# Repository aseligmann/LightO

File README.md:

# LightO

LightO is an open remote-controlled light project.

The project is based around an ESP32 driving a string of addressable LEDs, in this case a custom PCB with 61 SK6812 RGBW LEDs.

The user is able to control the LightO through an intuitive web-based interface, consisting of color-wheel and slider control.
The brightness of the light is user-controlled and can be driven at up to roughly 15 W, for an eye-scorching brightness level.

The LightO has 3 modes which can be selected from the interface:

* **Colour** - User defines a colour to display
* **Candle** - Simulates a flickering candle
* **Cycle** - Cycles through the colour-spectrum

The light is powered by a single USB-C port. 

### Images

### Features
- Full control of colour and brightness (RGBW channels) for all LEDs
- USB-C powered
- WiFi based control with user-centered design
- Intuitive captive AP for setup

### Development
- [ ] Provide schematic for ESP32 piggyback board
- [ ] Wake-up mode simulating a sunrise at a userdefined time
- [ ] Migrate code to PlatformIO
- [ ] Integrate USB-C PD and ESP32 on LED PCB

### Bill of Materials

#### PCB
* 1x 160 mm LightO PCB (light_160mm_v1_0_2020-04-21)
* 61x SK6812 LEDs
* 61x 5050 LED lenses, wide angle (optional)
* 61x 0805 100 nF capacitors
* 2x JST-XH 2-pin straight connectors

#### ESP32
* 1x ESP32 development board
* 1x 100 uF capacitor
* 2x 330 Ohm resistors

#### Power-delivery
* 1x USB-C PD module (ZY12PDN)

#### Misc.
* 7x M3 bolts (16 mm)
* 7x M3 nuts
* 3x 2.2x9.5 self-tapping screws

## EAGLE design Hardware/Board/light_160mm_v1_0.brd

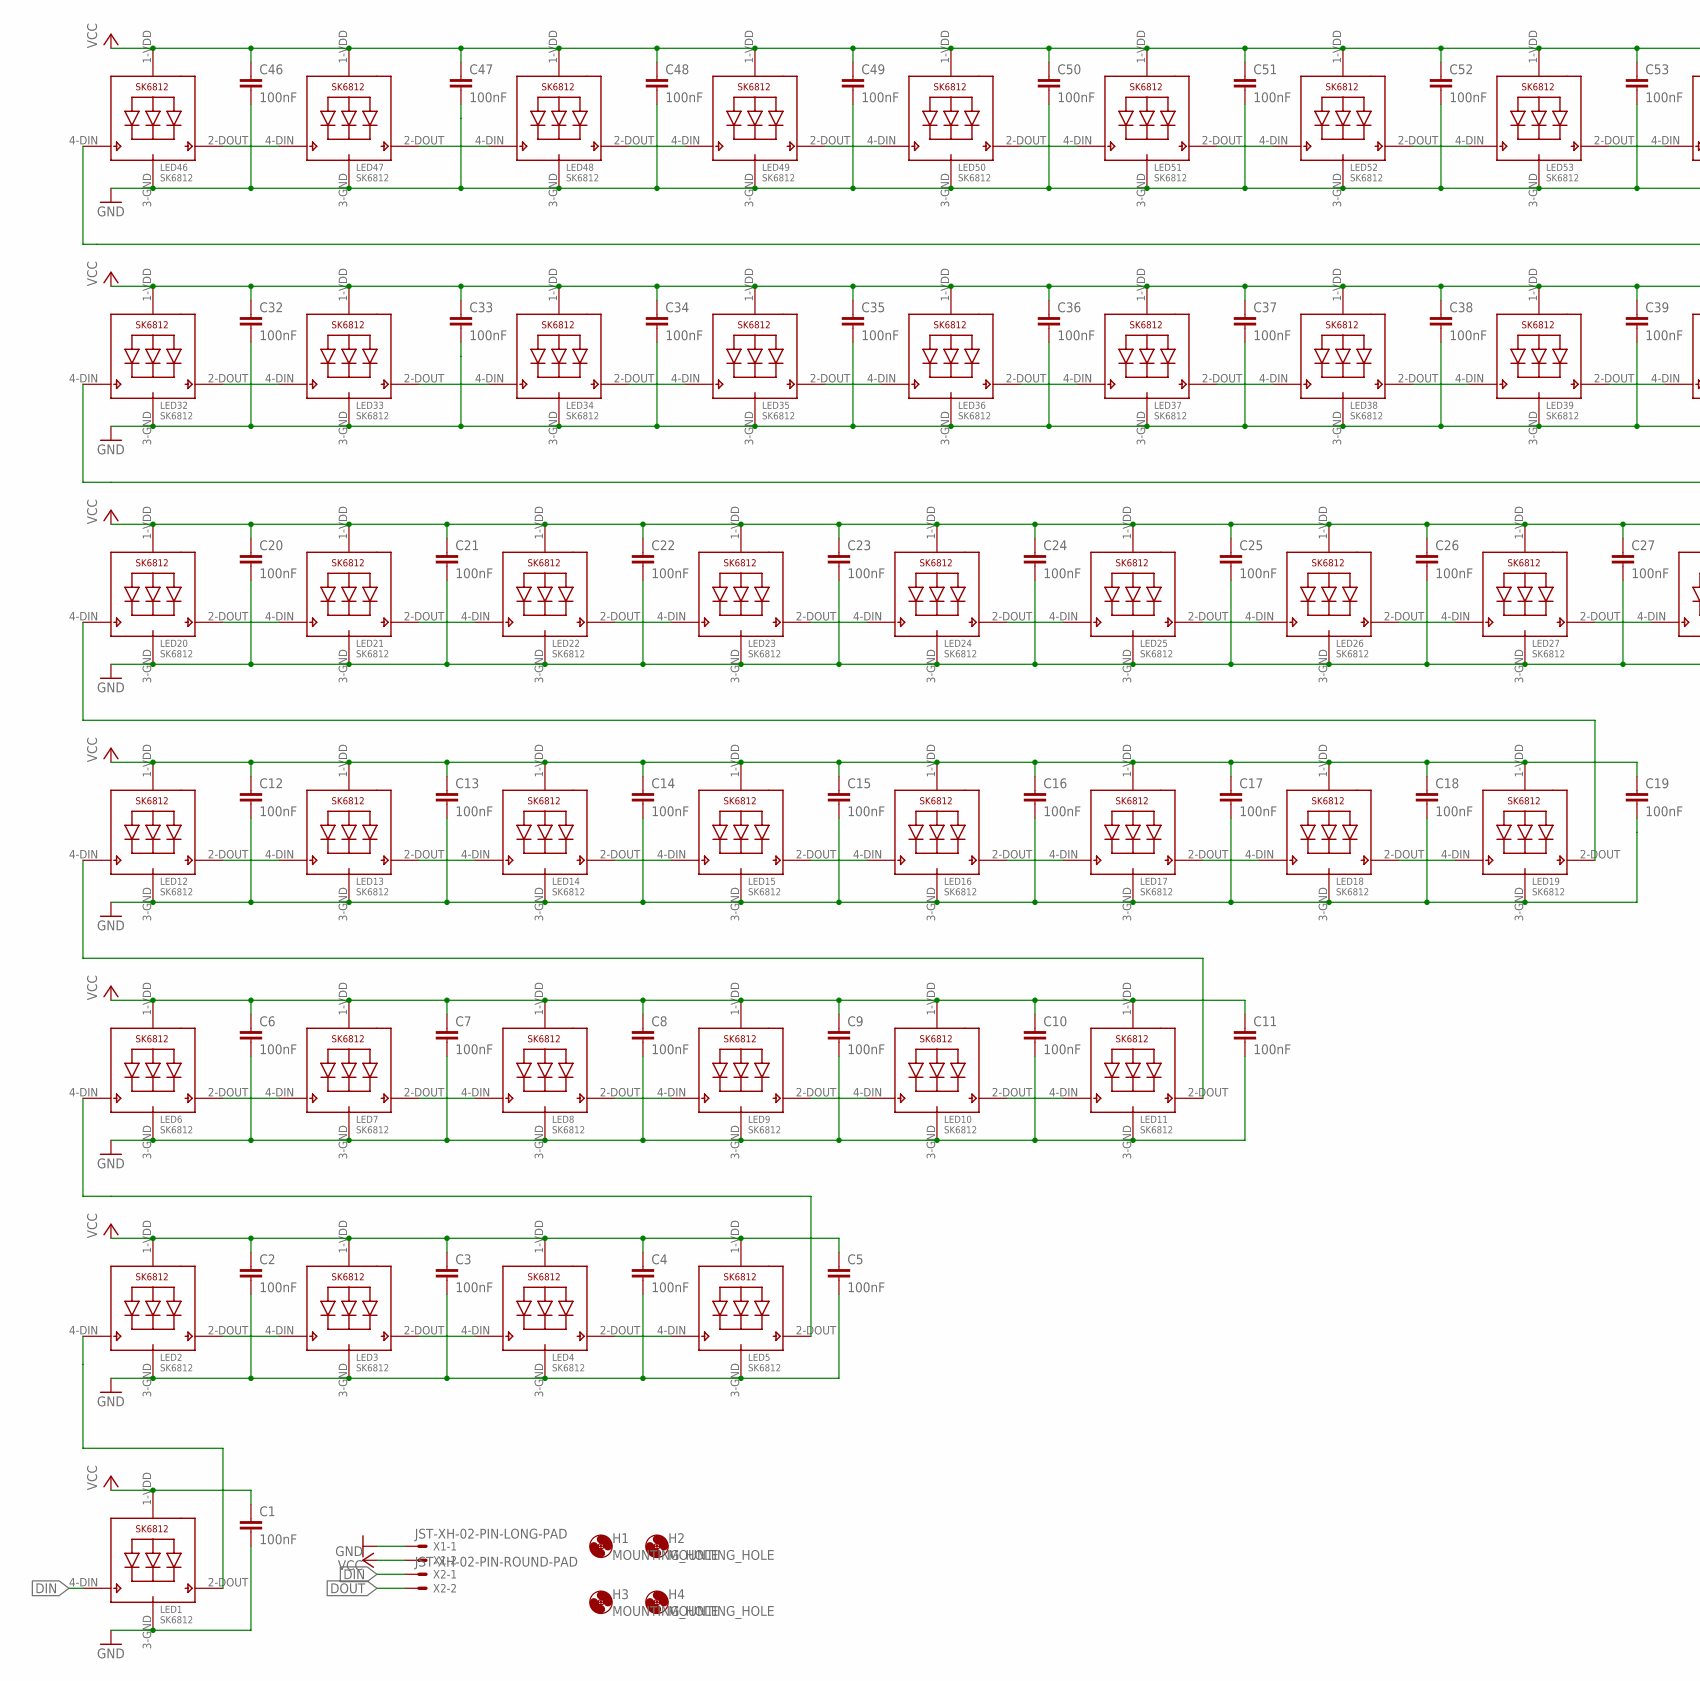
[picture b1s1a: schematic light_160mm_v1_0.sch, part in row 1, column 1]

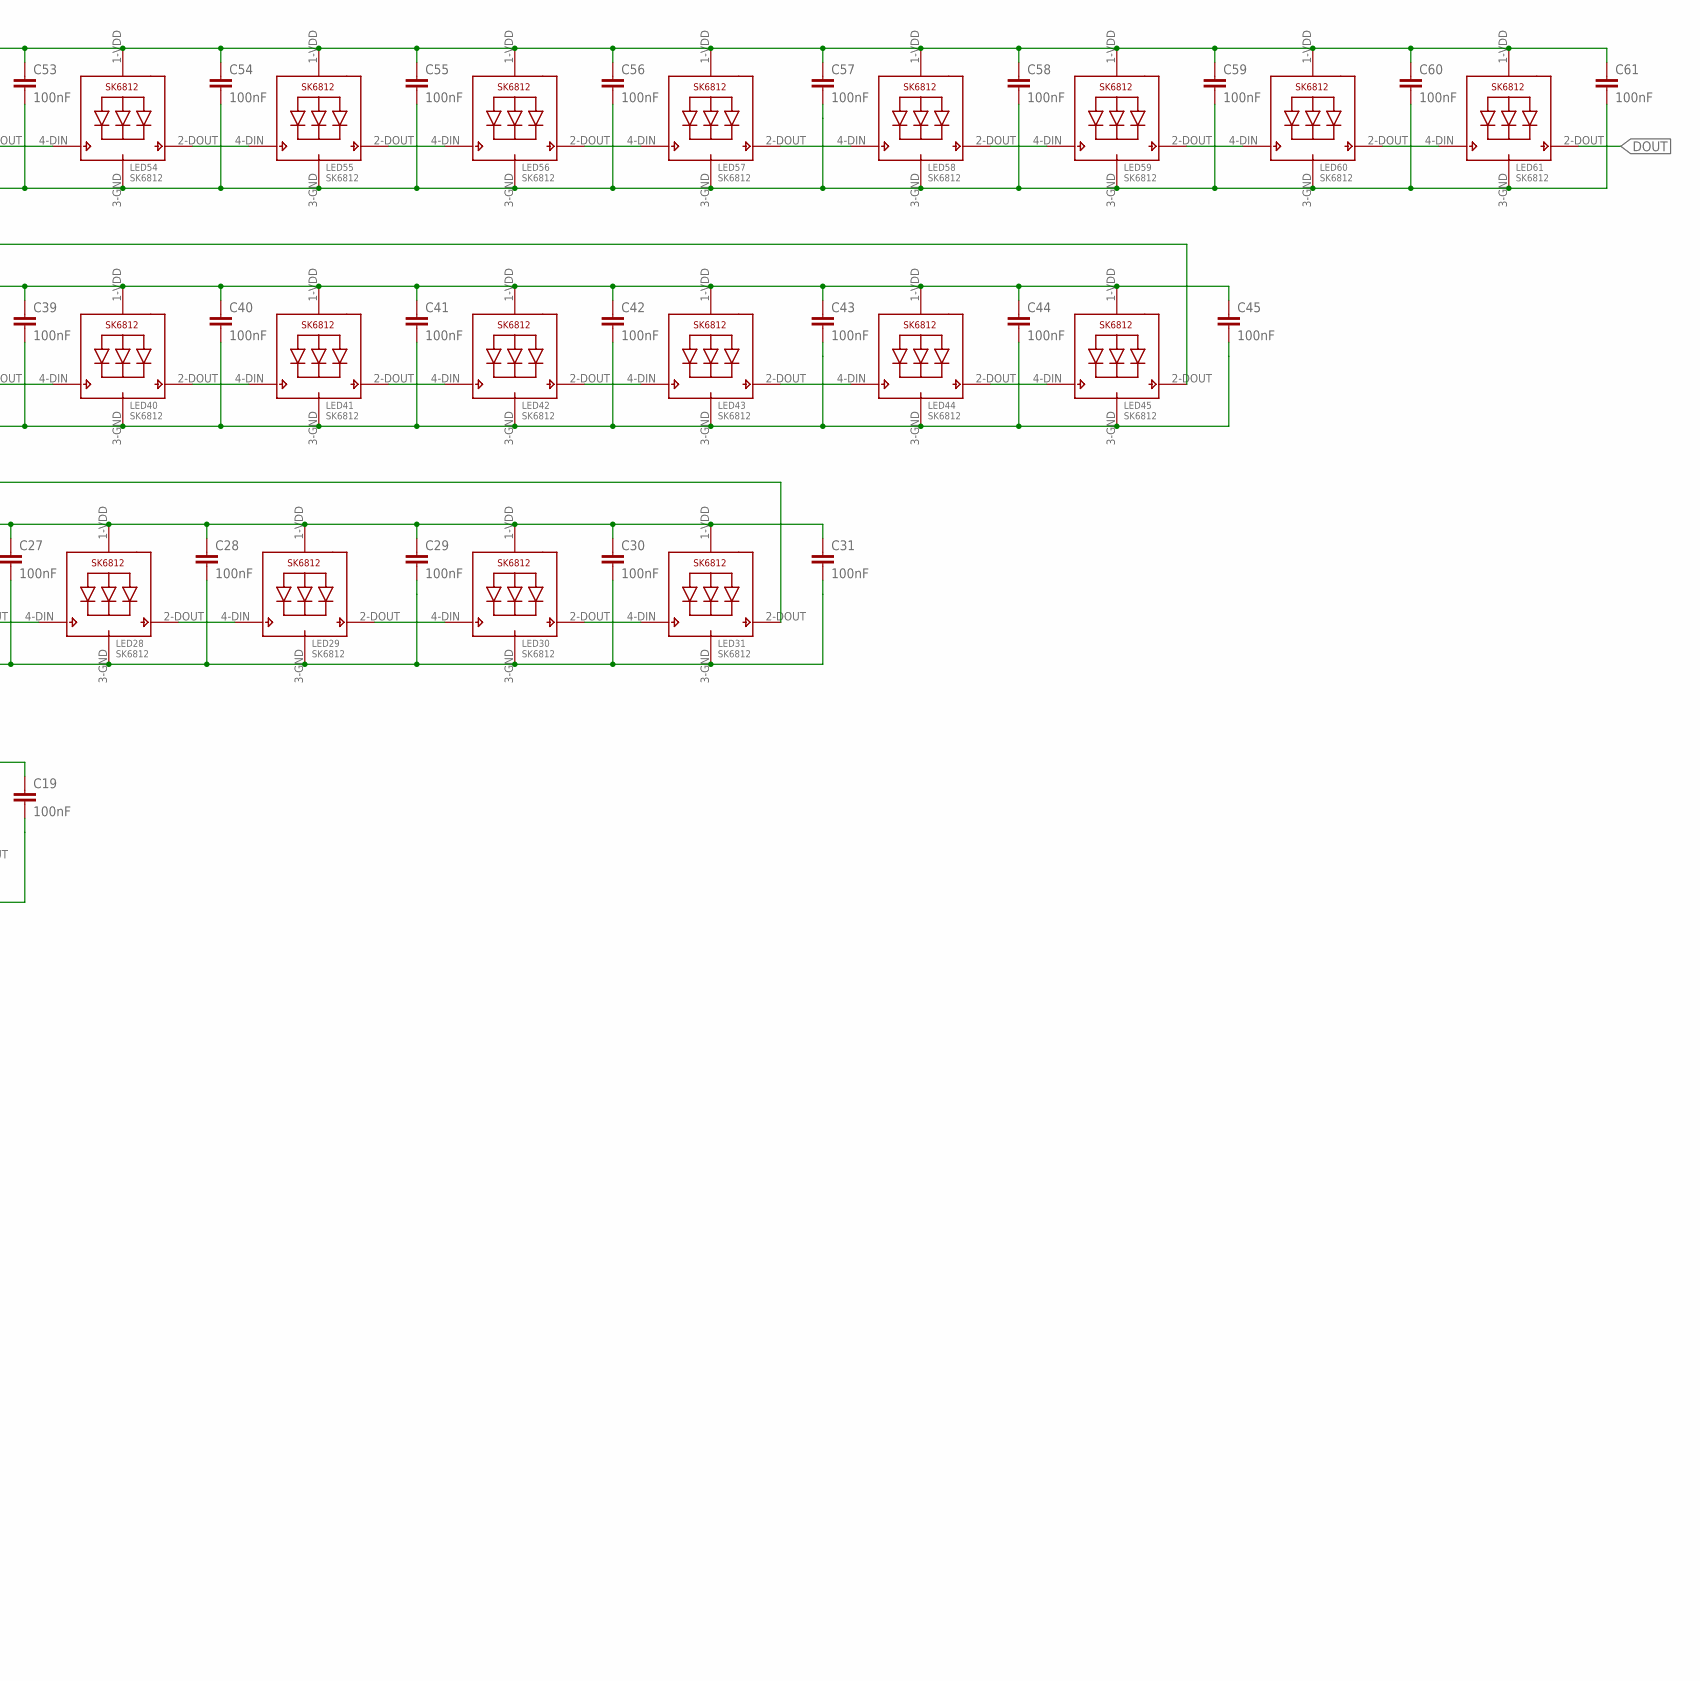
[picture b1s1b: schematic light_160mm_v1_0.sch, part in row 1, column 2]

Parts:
C1, C2, C3, C4, C5, C6, C7, C8, C9, C10, C11, C12, C13, C14, C15, C16, C17, C18, C19, C20, C21, C22, C23, C24, C25, C26, C27, C28, C29, C30, C31, C32, C33, C34, C35, C36, C37, C38, C39, C40, C41, C42, C43, C44, C45, C46, C47, C48, C49, C50, C51, C52, C53, C54, C55, C56, C57, C58, C59, C60, C61: 100nF; C0805
H1, H2, H3, H4: MOUNTING_HOLE; 4,1
LED1, LED2, LED3, LED4, LED5, LED6, LED7, LED8, LED9, LED10, LED11, LED12, LED13, LED14, LED15, LED16, LED17, LED18, LED19, LED20, LED21, LED22, LED23, LED24, LED25, LED26, LED27, LED28, LED29, LED30, LED31, LED32, LED33, LED34, LED35, LED36, LED37, LED38, LED39, LED40, LED41, LED42, LED43, LED44, LED45, LED46, LED47, LED48, LED49, LED50, LED51, LED52, LED53, LED54, LED55, LED56, LED57, LED58, LED59, LED60, LED61: SK6812; LED5050
X1: JST-XH-02-PIN-LONG-PAD; JST-XH-02-PACKAGE-LONG-PAD
X2: JST-XH-02-PIN-ROUND-PAD; JST-XH-02-PACKAGE-ROUND-PAD

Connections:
DIN: LED1.4-DIN (DI), X2.1
DOUT: LED61.2-DOUT (DO), X2.2
GND: C1.2, C2.2, C3.2, C4.2, C5.2, C6.2, C7.2, C8.2, C9.2, C10.2, C11.2, C12.2, C13.2, C14.2, C15.2, C16.2, C17.2, C18.2, C19.2, C20.2, C21.2, C22.2, C23.2, C24.2, C25.2, C26.2, C27.2, C28.2, C29.2, C30.2, C31.2, C32.2, C33.2, C34.2, C35.2, C36.2, C37.2, C38.2, C39.2, C40.2, C41.2, C42.2, C43.2, C44.2, C45.2, C46.2, C47.2, C48.2, C49.2, C50.2, C51.2, C52.2, C53.2, C54.2, C55.2, C56.2, C57.2, C58.2, C59.2, C60.2, C61.2, LED1.3-GND (GND), LED2.3-GND (GND), LED3.3-GND (GND), LED4.3-GND (GND), LED5.3-GND (GND), LED6.3-GND (GND), LED7.3-GND (GND), LED8.3-GND (GND), LED9.3-GND (GND), LED10.3-GND (GND), LED11.3-GND (GND), LED12.3-GND (GND), LED13.3-GND (GND), LED14.3-GND (GND), LED15.3-GND (GND), LED16.3-GND (GND), LED17.3-GND (GND), LED18.3-GND (GND), LED19.3-GND (GND), LED20.3-GND (GND), LED21.3-GND (GND), LED22.3-GND (GND), LED23.3-GND (GND), LED24.3-GND (GND), LED25.3-GND (GND), LED26.3-GND (GND), LED27.3-GND (GND), LED28.3-GND (GND), LED29.3-GND (GND), LED30.3-GND (GND), LED31.3-GND (GND), LED32.3-GND (GND), LED33.3-GND (GND), LED34.3-GND (GND), LED35.3-GND (GND), LED36.3-GND (GND), LED37.3-GND (GND), LED38.3-GND (GND), LED39.3-GND (GND), LED40.3-GND (GND), LED41.3-GND (GND), LED42.3-GND (GND), LED43.3-GND (GND), LED44.3-GND (GND), LED45.3-GND (GND), LED46.3-GND (GND), LED47.3-GND (GND), LED48.3-GND (GND), LED49.3-GND (GND), LED50.3-GND (GND), LED51.3-GND (GND), LED52.3-GND (GND), LED53.3-GND (GND), LED54.3-GND (GND), LED55.3-GND (GND), LED56.3-GND (GND), LED57.3-GND (GND), LED58.3-GND (GND), LED59.3-GND (GND), LED60.3-GND (GND), LED61.3-GND (GND), X1.1
unnamed: LED46.2-DOUT (DO), LED47.4-DIN (DI)
unnamed: LED47.2-DOUT (DO), LED48.4-DIN (DI)
unnamed: LED48.2-DOUT (DO), LED49.4-DIN (DI)
unnamed: LED49.2-DOUT (DO), LED50.4-DIN (DI)
unnamed: LED50.2-DOUT (DO), LED51.4-DIN (DI)
unnamed: LED51.2-DOUT (DO), LED52.4-DIN (DI)
unnamed: LED52.2-DOUT (DO), LED53.4-DIN (DI)
unnamed: LED53.2-DOUT (DO), LED54.4-DIN (DI)
unnamed: LED54.2-DOUT (DO), LED55.4-DIN (DI)
unnamed: LED55.2-DOUT (DO), LED56.4-DIN (DI)
unnamed: LED56.2-DOUT (DO), LED57.4-DIN (DI)
unnamed: LED57.2-DOUT (DO), LED58.4-DIN (DI)
unnamed: LED58.2-DOUT (DO), LED59.4-DIN (DI)
unnamed: LED59.2-DOUT (DO), LED60.4-DIN (DI)
unnamed: LED60.2-DOUT (DO), LED61.4-DIN (DI)
unnamed: LED11.2-DOUT (DO), LED12.4-DIN (DI)
unnamed: LED32.2-DOUT (DO), LED33.4-DIN (DI)
unnamed: LED33.2-DOUT (DO), LED34.4-DIN (DI)
unnamed: LED34.2-DOUT (DO), LED35.4-DIN (DI)
unnamed: LED35.2-DOUT (DO), LED36.4-DIN (DI)
unnamed: LED36.2-DOUT (DO), LED37.4-DIN (DI)
unnamed: LED37.2-DOUT (DO), LED38.4-DIN (DI)
unnamed: LED38.2-DOUT (DO), LED39.4-DIN (DI)
unnamed: LED39.2-DOUT (DO), LED40.4-DIN (DI)
unnamed: LED40.2-DOUT (DO), LED41.4-DIN (DI)
unnamed: LED41.2-DOUT (DO), LED42.4-DIN (DI)
unnamed: LED42.2-DOUT (DO), LED43.4-DIN (DI)
unnamed: LED43.2-DOUT (DO), LED44.4-DIN (DI)
unnamed: LED44.2-DOUT (DO), LED45.4-DIN (DI)
unnamed: LED19.2-DOUT (DO), LED20.4-DIN (DI)
unnamed: LED20.2-DOUT (DO), LED21.4-DIN (DI)
unnamed: LED21.2-DOUT (DO), LED22.4-DIN (DI)
unnamed: LED22.2-DOUT (DO), LED23.4-DIN (DI)
unnamed: LED23.2-DOUT (DO), LED24.4-DIN (DI)
unnamed: LED24.2-DOUT (DO), LED25.4-DIN (DI)
unnamed: LED25.2-DOUT (DO), LED26.4-DIN (DI)
unnamed: LED26.2-DOUT (DO), LED27.4-DIN (DI)
unnamed: LED27.2-DOUT (DO), LED28.4-DIN (DI)
unnamed: LED28.2-DOUT (DO), LED29.4-DIN (DI)
unnamed: LED29.2-DOUT (DO), LED30.4-DIN (DI)
unnamed: LED30.2-DOUT (DO), LED31.4-DIN (DI)
unnamed: LED31.2-DOUT (DO), LED32.4-DIN (DI)
unnamed: LED12.2-DOUT (DO), LED13.4-DIN (DI)
unnamed: LED13.2-DOUT (DO), LED14.4-DIN (DI)
unnamed: LED14.2-DOUT (DO), LED15.4-DIN (DI)
unnamed: LED15.2-DOUT (DO), LED16.4-DIN (DI)
unnamed: LED16.2-DOUT (DO), LED17.4-DIN (DI)
unnamed: LED17.2-DOUT (DO), LED18.4-DIN (DI)
unnamed: LED18.2-DOUT (DO), LED19.4-DIN (DI)
unnamed: LED45.2-DOUT (DO), LED46.4-DIN (DI)
unnamed: LED6.2-DOUT (DO), LED7.4-DIN (DI)
unnamed: LED7.2-DOUT (DO), LED8.4-DIN (DI)
unnamed: LED8.2-DOUT (DO), LED9.4-DIN (DI)
unnamed: LED9.2-DOUT (DO), LED10.4-DIN (DI)
unnamed: LED10.2-DOUT (DO), LED11.4-DIN (DI)
unnamed: LED1.2-DOUT (DO), LED2.4-DIN (DI)
unnamed: LED2.2-DOUT (DO), LED3.4-DIN (DI)
unnamed: LED3.2-DOUT (DO), LED4.4-DIN (DI)
unnamed: LED4.2-DOUT (DO), LED5.4-DIN (DI)
unnamed: LED5.2-DOUT (DO), LED6.4-DIN (DI)
VCC: C1.1, C2.1, C3.1, C4.1, C5.1, C6.1, C7.1, C8.1, C9.1, C10.1, C11.1, C12.1, C13.1, C14.1, C15.1, C16.1, C17.1, C18.1, C19.1, C20.1, C21.1, C22.1, C23.1, C24.1, C25.1, C26.1, C27.1, C28.1, C29.1, C30.1, C31.1, C32.1, C33.1, C34.1, C35.1, C36.1, C37.1, C38.1, C39.1, C40.1, C41.1, C42.1, C43.1, C44.1, C45.1, C46.1, C47.1, C48.1, C49.1, C50.1, C51.1, C52.1, C53.1, C54.1, C55.1, C56.1, C57.1, C58.1, C59.1, C60.1, C61.1, LED1.1-VDD (VDD), LED2.1-VDD (VDD), LED3.1-VDD (VDD), LED4.1-VDD (VDD), LED5.1-VDD (VDD), LED6.1-VDD (VDD), LED7.1-VDD (VDD), LED8.1-VDD (VDD), LED9.1-VDD (VDD), LED10.1-VDD (VDD), LED11.1-VDD (VDD), LED12.1-VDD (VDD), LED13.1-VDD (VDD), LED14.1-VDD (VDD), LED15.1-VDD (VDD), LED16.1-VDD (VDD), LED17.1-VDD (VDD), LED18.1-VDD (VDD), LED19.1-VDD (VDD), LED20.1-VDD (VDD), LED21.1-VDD (VDD), LED22.1-VDD (VDD), LED23.1-VDD (VDD), LED24.1-VDD (VDD), LED25.1-VDD (VDD), LED26.1-VDD (VDD), LED27.1-VDD (VDD), LED28.1-VDD (VDD), LED29.1-VDD (VDD), LED30.1-VDD (VDD), LED31.1-VDD (VDD), LED32.1-VDD (VDD), LED33.1-VDD (VDD), LED34.1-VDD (VDD), LED35.1-VDD (VDD), LED36.1-VDD (VDD), LED37.1-VDD (VDD), LED38.1-VDD (VDD), LED39.1-VDD (VDD), LED40.1-VDD (VDD), LED41.1-VDD (VDD), LED42.1-VDD (VDD), LED43.1-VDD (VDD), LED44.1-VDD (VDD), LED45.1-VDD (VDD), LED46.1-VDD (VDD), LED47.1-VDD (VDD), LED48.1-VDD (VDD), LED49.1-VDD (VDD), LED50.1-VDD (VDD), LED51.1-VDD (VDD), LED52.1-VDD (VDD), LED53.1-VDD (VDD), LED54.1-VDD (VDD), LED55.1-VDD (VDD), LED56.1-VDD (VDD), LED57.1-VDD (VDD), LED58.1-VDD (VDD), LED59.1-VDD (VDD), LED60.1-VDD (VDD), LED61.1-VDD (VDD), X1.2

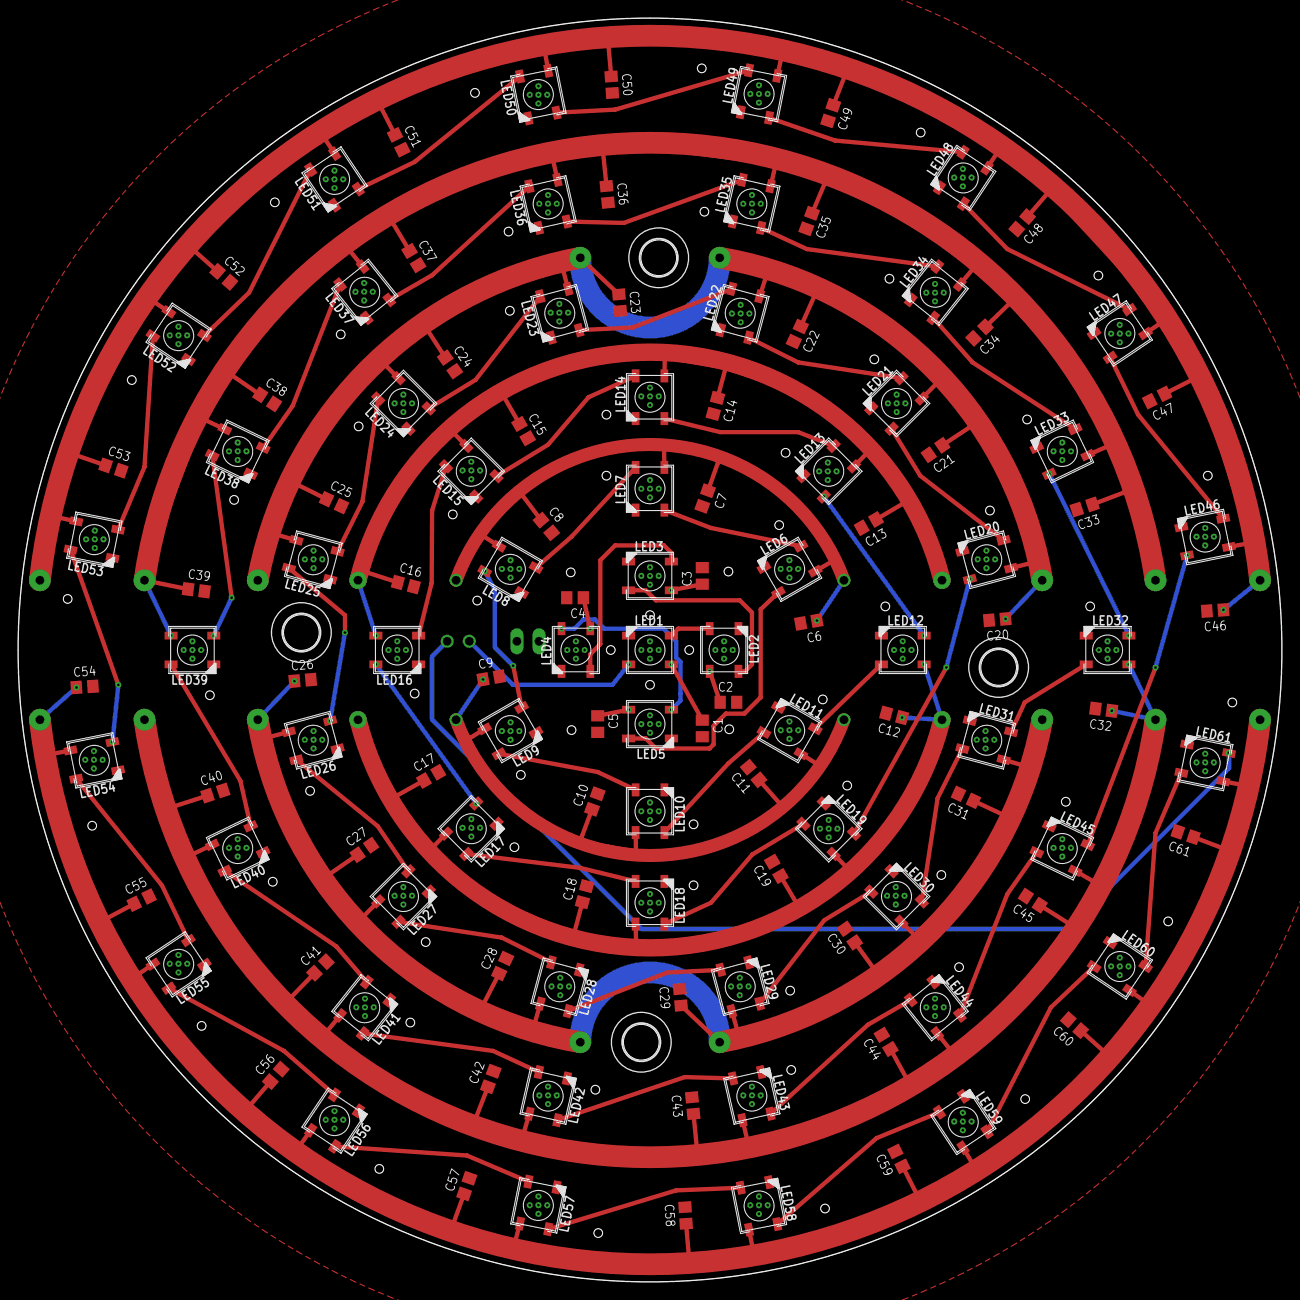
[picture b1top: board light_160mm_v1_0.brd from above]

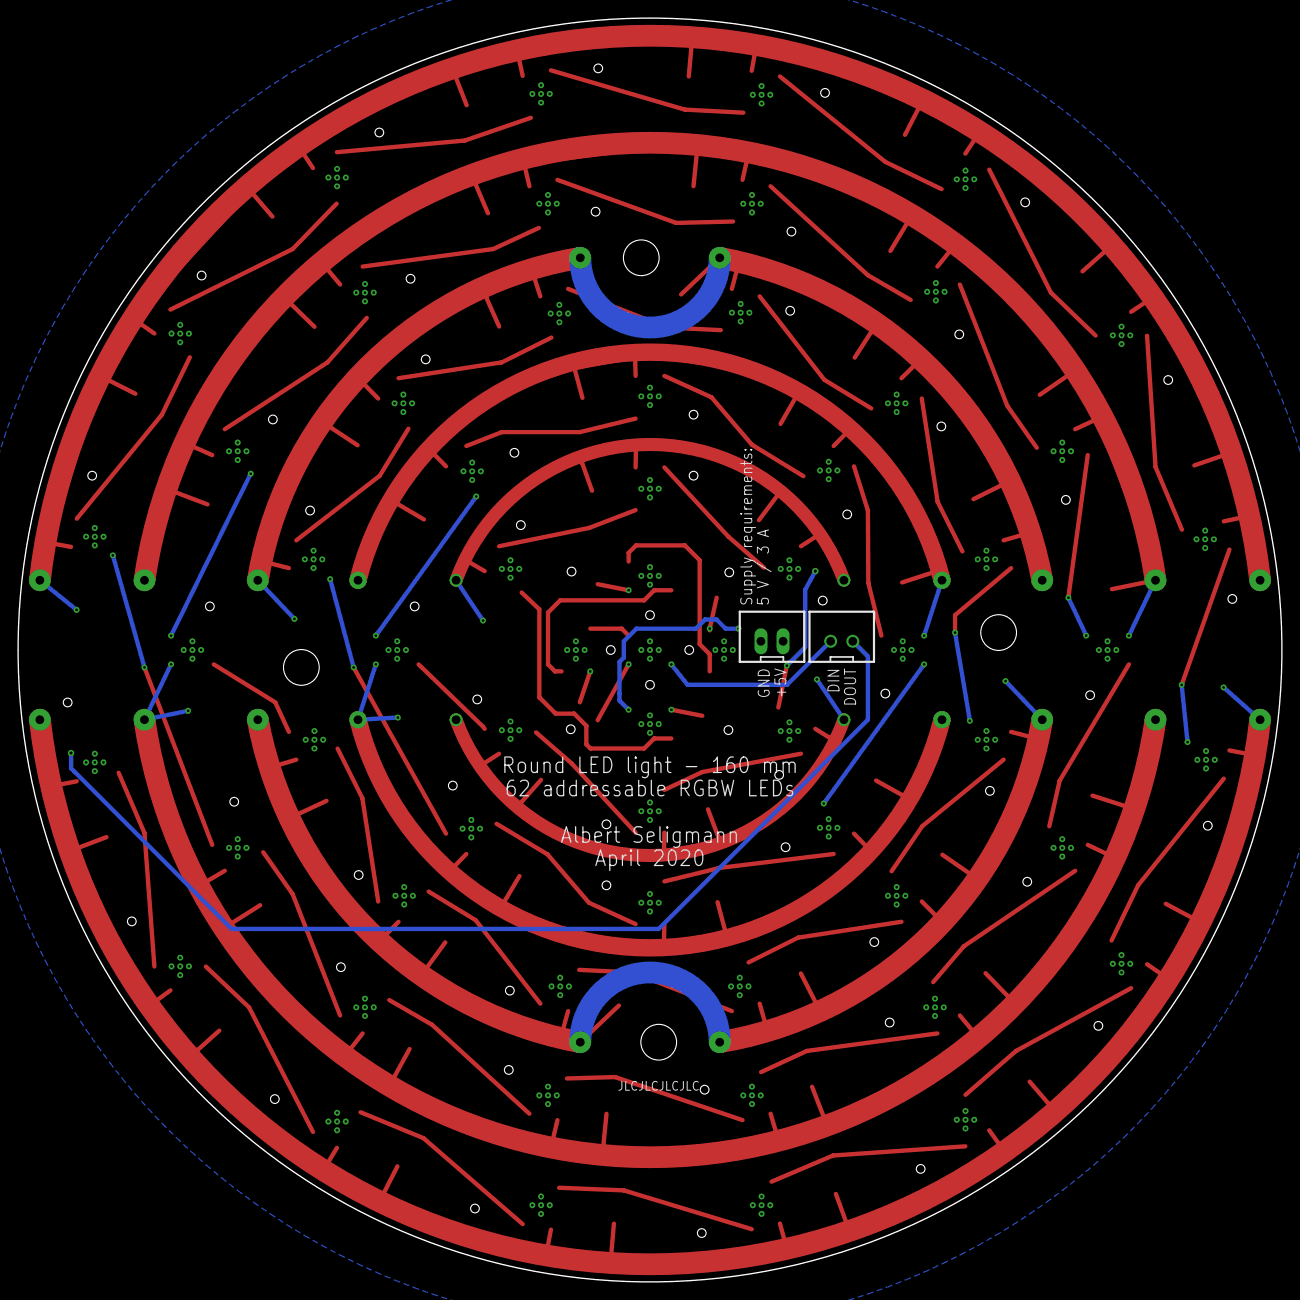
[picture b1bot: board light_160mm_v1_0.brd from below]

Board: 2 copper layers, 145.0 x 145.0 mm, 128 parts (2 on the bottom side), 64 nets.

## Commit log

2020-09-02 Add captive WiFi AP config on boot-up to configure new network to connect to
2020-09-02 Clean up the code a bit
2020-09-02 Add webpage get state of LEDs on load
2020-09-02 Further cleanup
2020-09-02 Create LICENSE
2020-12-20 Complete overhaul. Add additional features, add test program, add additional parts, add images, update readme
2020-12-25 Add visual feedback on boot progress
2020-12-25 Remove unnecessary comments
2025-08-05 Add WLED ledmap for matrix support
    https://kno.wled.ge/advanced/mapping/
